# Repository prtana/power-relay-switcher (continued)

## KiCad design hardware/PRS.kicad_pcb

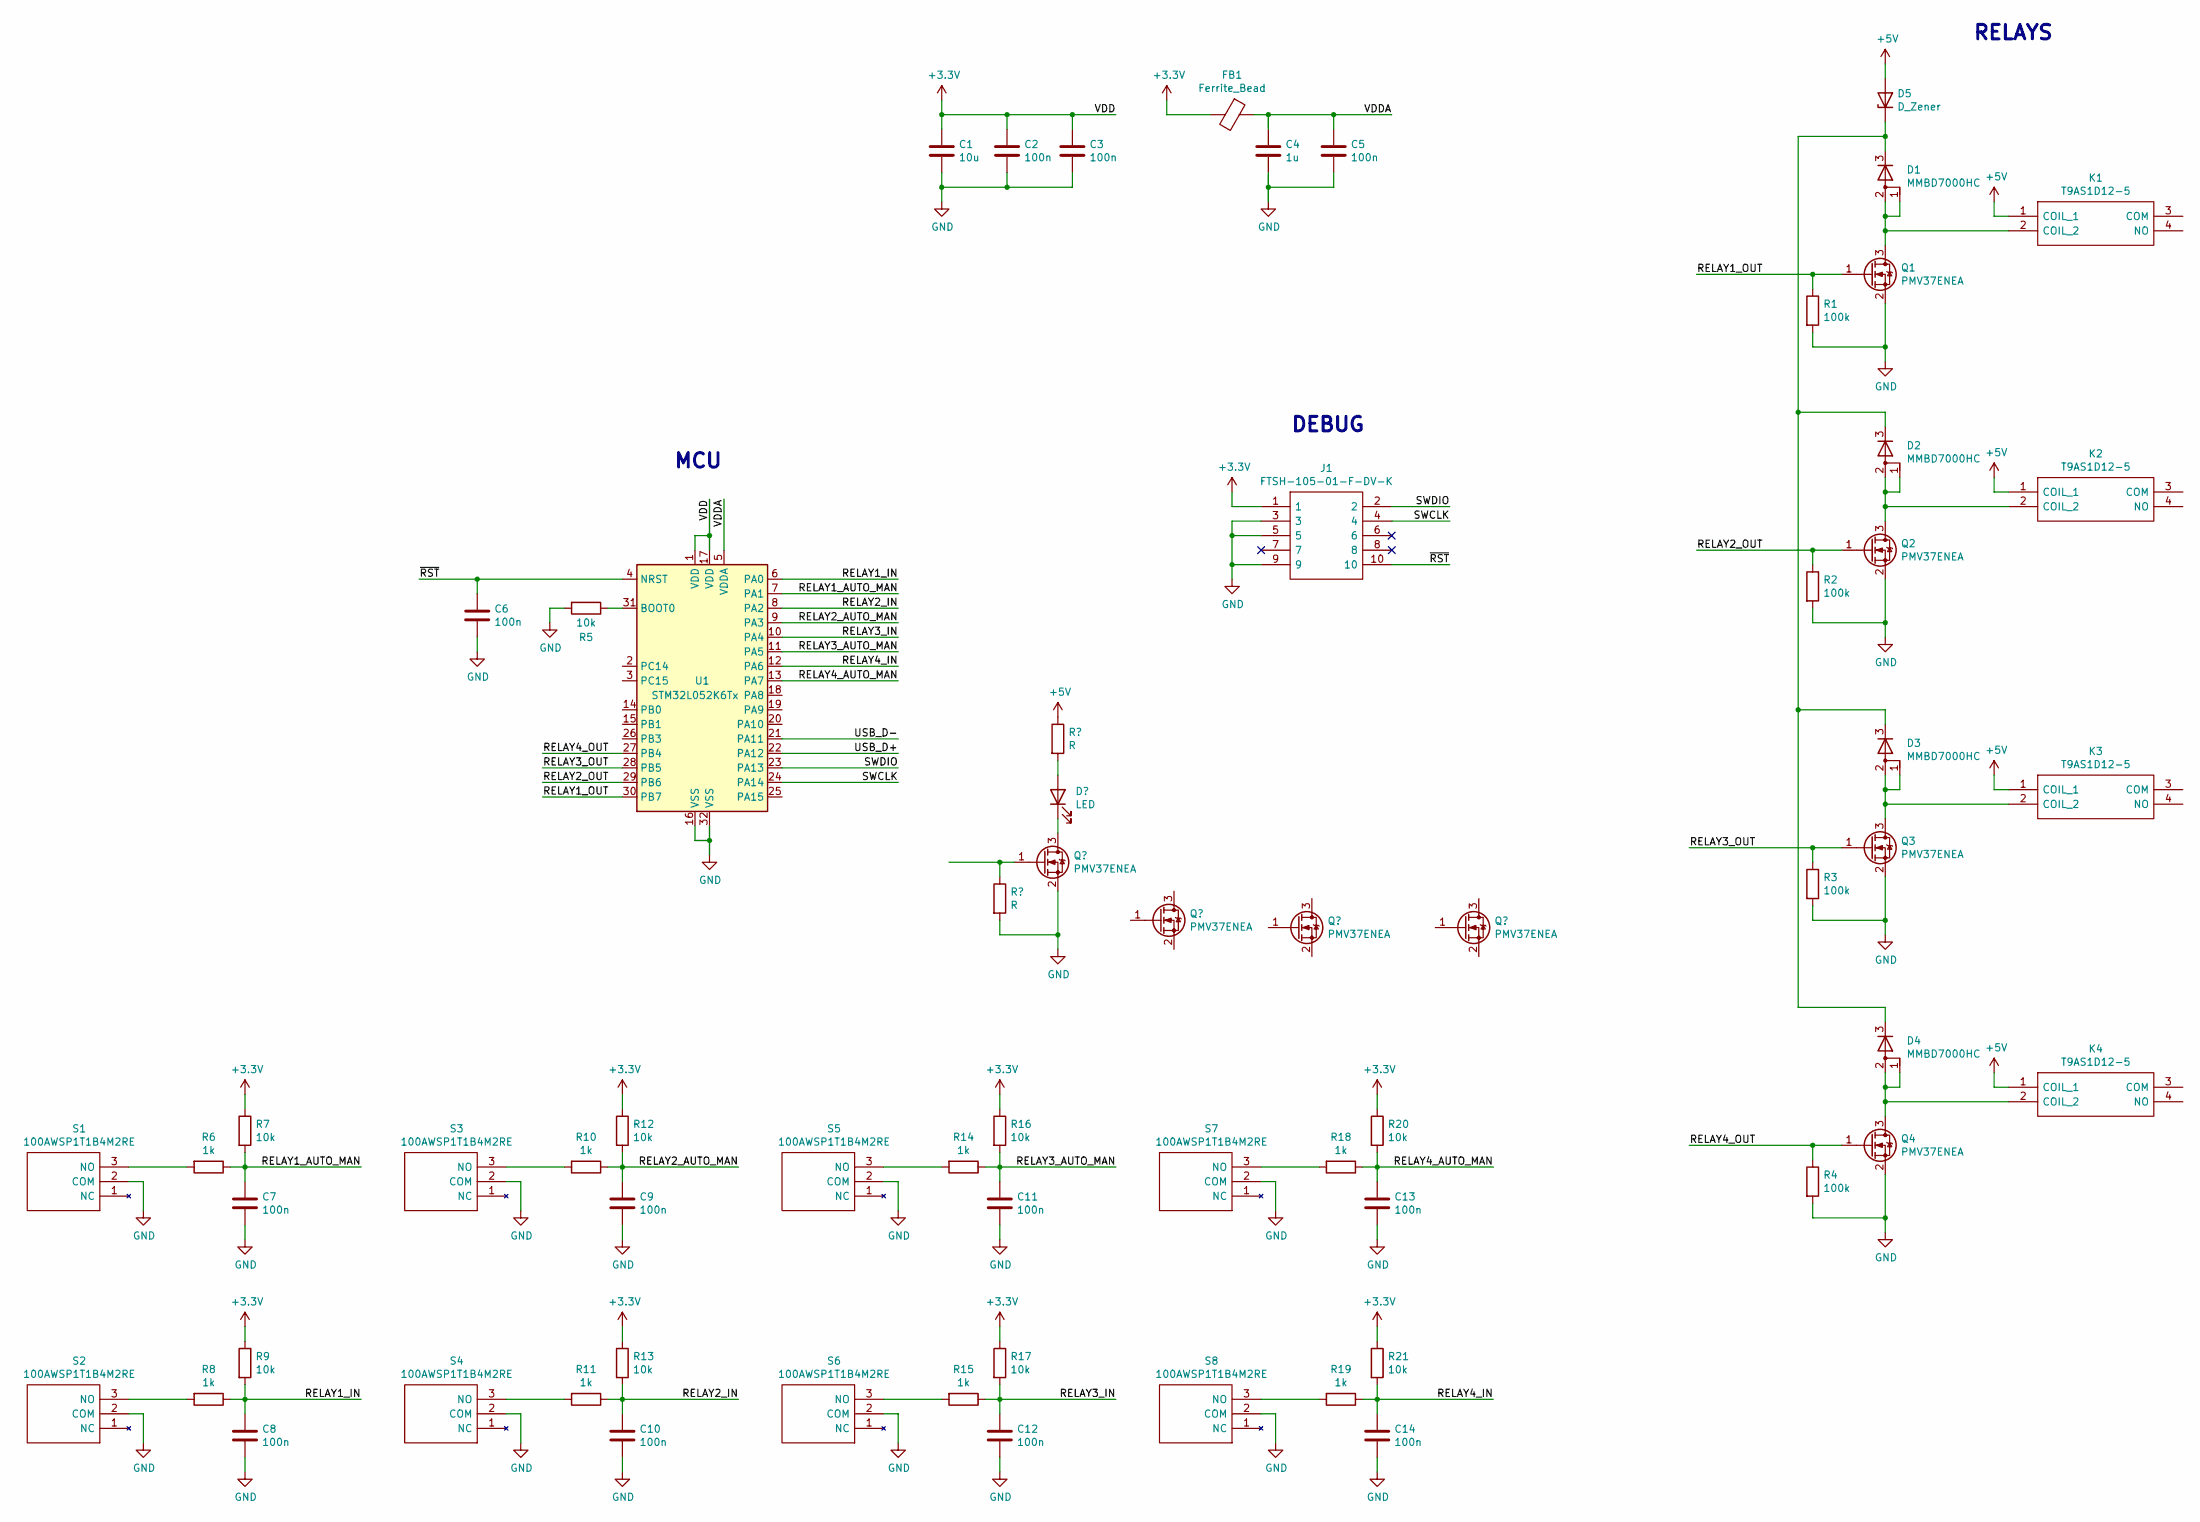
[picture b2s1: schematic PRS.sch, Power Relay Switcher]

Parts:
C1: 10u; C_0805_2012Metric_Pad1.18x1.45mm_HandSolder
C2, C3, C5, C6, C7, C8, C9, C10, C11, C12, C13, C14: 100n; C_0603_1608Metric_Pad1.08x0.95mm_HandSolder
C4: 1u; C_0603_1608Metric_Pad1.08x0.95mm_HandSolder
D1, D2, D3, D4: MMBD7000HC; SOT-23_Handsoldering
D5: D_Zener; D_SMA_Handsoldering
FB1: Ferrite_Bead; R_0603_1608Metric_Pad0.98x0.95mm_HandSolder
J1: FTSH-105-01-F-DV-K; FTSH-105-XX-YYY-DV-K-P; Manufacturer_Part_Number FTSH-105-01-F-DV-K-P; Mouser Part Number 200-FTSH10501FDVKP
K1, K2, K3, K4: T9AS1D12-5; T9AS1D125; Manufacturer_Part_Number T9AS1D12-5; Mouser Part Number 655-T9AS1D12-5
Q1, Q2, Q3, Q4: PMV37ENEA; SOT-23_Handsoldering
R1, R2, R3, R4: 100k; R_0603_1608Metric_Pad0.98x0.95mm_HandSolder
R5, R7, R9, R12, R13, R16, R17, R20, R21: 10k; R_0603_1608Metric_Pad0.98x0.95mm_HandSolder
R6, R8, R10, R11, R14, R15, R18, R19: 1k; R_0603_1608Metric_Pad0.98x0.95mm_HandSolder
S1, S2, S3, S4, S5, S6, S7, S8: 100AWSP1T1B4M2RE; Manufacturer_Part_Number 100AWSP1T1B4M2RE; Mouser Part Number 612-100A-A1422
U1: STM32L052K6Tx; LQFP-32_7x7mm_P0.8mm

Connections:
+3V3: C1.1, C2.1, C3.1, FB1.2, J1.1, R7.1, R9.1, R12.1, R13.1, R16.1, R17.1, R20.1, R21.1, U1.1 (VDD), U1.17 (VDD)
+5V: D5.2 (A), K1.1 (COIL_1), K2.1 (COIL_1), K3.1 (COIL_1), K4.1 (COIL_1)
/RELAY1_AUTO_MAN: C7.1, R6.1, R7.2, U1.7 (PA1)
/RELAY1_IN: C8.1, R8.1, R9.2, U1.6 (PA0)
/RELAY1_OUT: Q1.1 (G), R1.1, U1.30 (PB7)
/RELAY2_AUTO_MAN: C9.1, R10.1, R12.2, U1.9 (PA3)
/RELAY2_IN: C10.1, R11.1, R13.2, U1.8 (PA2)
/RELAY2_OUT: Q2.1 (G), R2.1, U1.29 (PB6)
/RELAY3_AUTO_MAN: C11.1, R14.1, R16.2, U1.11 (PA5)
/RELAY3_IN: C12.1, R15.1, R17.2, U1.10 (PA4)
/RELAY3_OUT: Q3.1 (G), R3.1, U1.28 (PB5)
/RELAY4_AUTO_MAN: C13.1, R18.1, R20.2, U1.13 (PA7)
/RELAY4_IN: C14.1, R19.1, R21.2, U1.12 (PA6)
/RELAY4_OUT: Q4.1 (G), R4.1, U1.27 (PB4)
/SWCLK: J1.4, U1.24 (PA14)
/SWDIO: J1.2, U1.23 (PA13)
/USB_D+: U1.22 (PA12)
/USB_D-: U1.21 (PA11)
/VDDA: C4.1, C5.1, FB1.1, U1.5 (VDDA)
/~RST: C6.1, J1.10, U1.4 (NRST)
GND: C1.2, C2.2, C3.2, C4.2, C5.2, C6.2, C7.2, C8.2, C9.2, C10.2, C11.2, C12.2, C13.2, C14.2, J1.3, J1.5, J1.9, Q1.2 (S), Q2.2 (S), Q3.2 (S), Q4.2 (S), R1.2, R2.2, R3.2, R4.2, R5.2, S1.2 (COM), S2.2 (COM), S3.2 (COM), S4.2 (COM), S5.2 (COM), S6.2 (COM), S7.2 (COM), S8.2 (COM), U1.16 (VSS), U1.32 (VSS)
unnamed: D1.1 (A), D1.2 (A), K1.2 (COIL_2), Q1.3 (D)
unnamed: D1.3 (K), D2.3 (K), D3.3 (K), D4.3 (K), D5.1 (K)
unnamed: D2.1 (A), D2.2 (A), K2.2 (COIL_2), Q2.3 (D)
unnamed: D3.1 (A), D3.2 (A), K3.2 (COIL_2), Q3.3 (D)
unnamed: D4.1 (A), D4.2 (A), K4.2 (COIL_2), Q4.3 (D)
unnamed: R5.1, U1.31 (BOOT0)
unnamed: R6.2, S1.3 (NO)
unnamed: R8.2, S2.3 (NO)
unnamed: R10.2, S3.3 (NO)
unnamed: R11.2, S4.3 (NO)
unnamed: R14.2, S5.3 (NO)
unnamed: R15.2, S6.3 (NO)
unnamed: R18.2, S7.3 (NO)
unnamed: R19.2, S8.3 (NO)

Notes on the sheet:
DEBUG
MCU
RELAYS

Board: 2 copper layers, 59 parts (0 on the bottom side), 33 nets, no tracks yet.

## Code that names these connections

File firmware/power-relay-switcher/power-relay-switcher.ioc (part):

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Mcu.Name=STM32L062K8Tx
Mcu.Package=LQFP32
Mcu.UserName=STM32L062K8Tx
PA0.GPIOParameters=GPIO_Label,GPIO_ModeDefaultEXTI
PA0.GPIO_Label=RELAY_1_USB_MAN
PA0.GPIO_ModeDefaultEXTI=GPIO_MODE_IT_RISING_FALLING
PA0.Signal=GPXTI0
PA1.GPIOParameters=GPIO_Label,GPIO_ModeDefaultEXTI
PA1.GPIO_Label=RELAY_1_IN
PA1.GPIO_ModeDefaultEXTI=GPIO_MODE_IT_RISING_FALLING
PA1.Signal=GPXTI1
PA11.Mode=Device
PA11.Signal=USB_DM
PA12.Mode=Device
PA12.Signal=USB_DP
PA13.Mode=Serial_Wire
PA13.Signal=SYS_SWDIO
PA14.Mode=Serial_Wire
PA14.Signal=SYS_SWCLK
PA2.GPIOParameters=GPIO_Label,GPIO_ModeDefaultEXTI
PA2.GPIO_Label=RELAY_2_USB_MAN
PA2.GPIO_ModeDefaultEXTI=GPIO_MODE_IT_RISING_FALLING
PA2.Signal=GPXTI2
PA3.GPIOParameters=GPIO_Label,GPIO_ModeDefaultEXTI
PA3.GPIO_Label=RELAY_2_IN
PA3.GPIO_ModeDefaultEXTI=GPIO_MODE_IT_RISING_FALLING
PA3.Signal=GPXTI3
PA4.GPIOParameters=GPIO_Label,GPIO_ModeDefaultEXTI
PA4.GPIO_Label=RELAY_3_USB_MAN
PA4.GPIO_ModeDefaultEXTI=GPIO_MODE_IT_RISING_FALLING
PA4.Signal=GPXTI4
PA5.GPIOParameters=GPIO_Label,GPIO_ModeDefaultEXTI
PA5.GPIO_Label=RELAY_3_IN
PA5.GPIO_ModeDefaultEXTI=GPIO_MODE_IT_RISING_FALLING
PA5.Signal=GPXTI5
PA6.GPIOParameters=GPIO_Label,GPIO_ModeDefaultEXTI
PA6.GPIO_Label=RELAY_4_USB_MAN
PA6.GPIO_ModeDefaultEXTI=GPIO_MODE_IT_RISING_FALLING
PA6.Signal=GPXTI6
PA7.GPIOParameters=GPIO_Label,GPIO_ModeDefaultEXTI
PA7.GPIO_Label=RELAY_4_IN
PA7.GPIO_ModeDefaultEXTI=GPIO_MODE_IT_RISING_FALLING
PA7.Signal=GPXTI7
PA8.GPIOParameters=GPIO_Label
PA8.GPIO_Label=RELAY_1_OUT
PA8.Signal=GPIO_Output
PA9.GPIOParameters=GPIO_Label
PA9.GPIO_Label=RELAY_2_OUT
PA9.Signal=GPIO_Output
PB0.GPIOParameters=GPIO_Label
PB0.GPIO_Label=RELAY_4_OUT
PB0.Signal=GPIO_Output
PB1.GPIOParameters=GPIO_Label
PB1.GPIO_Label=RELAY_3_OUT
PB1.Signal=GPIO_Output
PB3.GPIOParameters=GPIO_Label
PB3.GPIO_Label=FAN_CTRL
PB3.Signal=GPIO_Output
PB4.GPIOParameters=GPIO_Label
PB4.GPIO_Label=FAN_TACH
PB4.Signal=GPIO_Input
PB6.Mode=I2C
PB6.Signal=I2C1_SCL
PB7.Mode=I2C
PB7.Signal=I2C1_SDA
RCC.SYSCLKFreq_VALUE=16000000
RCC.SYSCLKSource=RCC_SYSCLKSOURCE_HSI
board=custom

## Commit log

2021-10-02 KiCad default project
2021-10-02 Add .gitignore
2021-10-02 Add relays
2021-10-02 Add Reference Materials
2021-10-12 Add fp-info-cache
2021-10-12 Add fp-lib-table
2021-10-12 Add sym-lyb-table
2021-10-12 Remove sym-lib-table as unnecessary
2021-10-12 Add sym-lib-table
2021-10-12 Remove fp-info-cache as unnecessary
2021-10-12 Touched up relay schematics
2021-10-12 Set resistor descriptions
2021-10-12 Add Fan connector
2021-10-12 Distributed schematic between sheets
2021-10-12 Set component description
2021-10-12 Set component values
2021-10-12 Add Temperature sensor datasheet
2021-10-12 Rename relay datasheet
2021-10-12 Remove PRS_front_panel as design is consolidated into single PCB
2021-10-12 Set zener diode PN
2021-10-12 Replace MCU with a larger Flash equivalent
2021-10-13 Add BOM
2021-10-13 Change C13 footprint
2021-10-13 Decreased LED resistor values
2021-10-13 Fixed broken wire
2021-10-15 Change C13 footprint to 1206
2021-10-16 Create PCB Layout
2022-01-12 Remove manually deleted files
2022-01-12 Add PRS_front_panel KiCad project & Gerbers
2022-01-12 Add Gerbers
2022-01-12 Add PRS_rear_panel KiCad project & Gerbers
2022-01-15 Move to directory 3D
2022-01-15 Add PRS_relay_board.step
2022-01-15 Move to directory KiCad
2022-01-15 Move to KiCad/
2022-01-15 Add PDF schematic
2022-01-15 Add STM32 project
2022-01-15 Remove Debug/
2022-01-15 Add InitRelayStructs()
2022-01-15 Add ReadSwitchManualUsbState
2022-01-15 Add SetRelayInitialPosition
2022-01-29 Toggle relays via switch interrupts
2022-01-30 Add USB TX functionality
2023-02-07 Upgrade to v6 KiCad
2023-02-07 Remove KiCad v5 schematic files
2023-02-08 Add KiCad v6 schematic files
2023-02-08 Remove KiCad v5 project file
2023-02-08 Add KiCad v6 project file
2023-02-08 Remove symbol library table & footprint library table
2023-02-08 Update PRS_relay_board.kicad_pcb to KiCad v6
2023-02-08 Update PRS_front_panel to KiCad v6
2023-02-08 Update PRS_rear_panel to KiCad v6
2023-02-14 Add STCN75 driver
2023-02-17 Read temp every second using RTC
2023-02-17 Set overlimit and hysteresis temperatures
2023-02-17 Add fan control
2023-02-19 Fix temperature checking
2023-02-20 Set fan resistor values
2023-02-20 Fix 3d model paths
2023-02-20 Update BOM
2023-02-20 Add missing HAL drivers
2023-02-21 Add basic SCPI functionality
2023-02-27 Add SCPI ROUTE functionality
2023-02-27 Add PUTTY image
2023-02-27 Add PUTTY image 2
2023-02-27 Add PUTTY example image
2023-02-27 Add images
2023-03-01 Add PCB 3D images
2023-03-03 Add STM32CubeIDE project files
